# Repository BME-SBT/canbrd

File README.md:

# canbrd
Universal CAN enabled MCU board

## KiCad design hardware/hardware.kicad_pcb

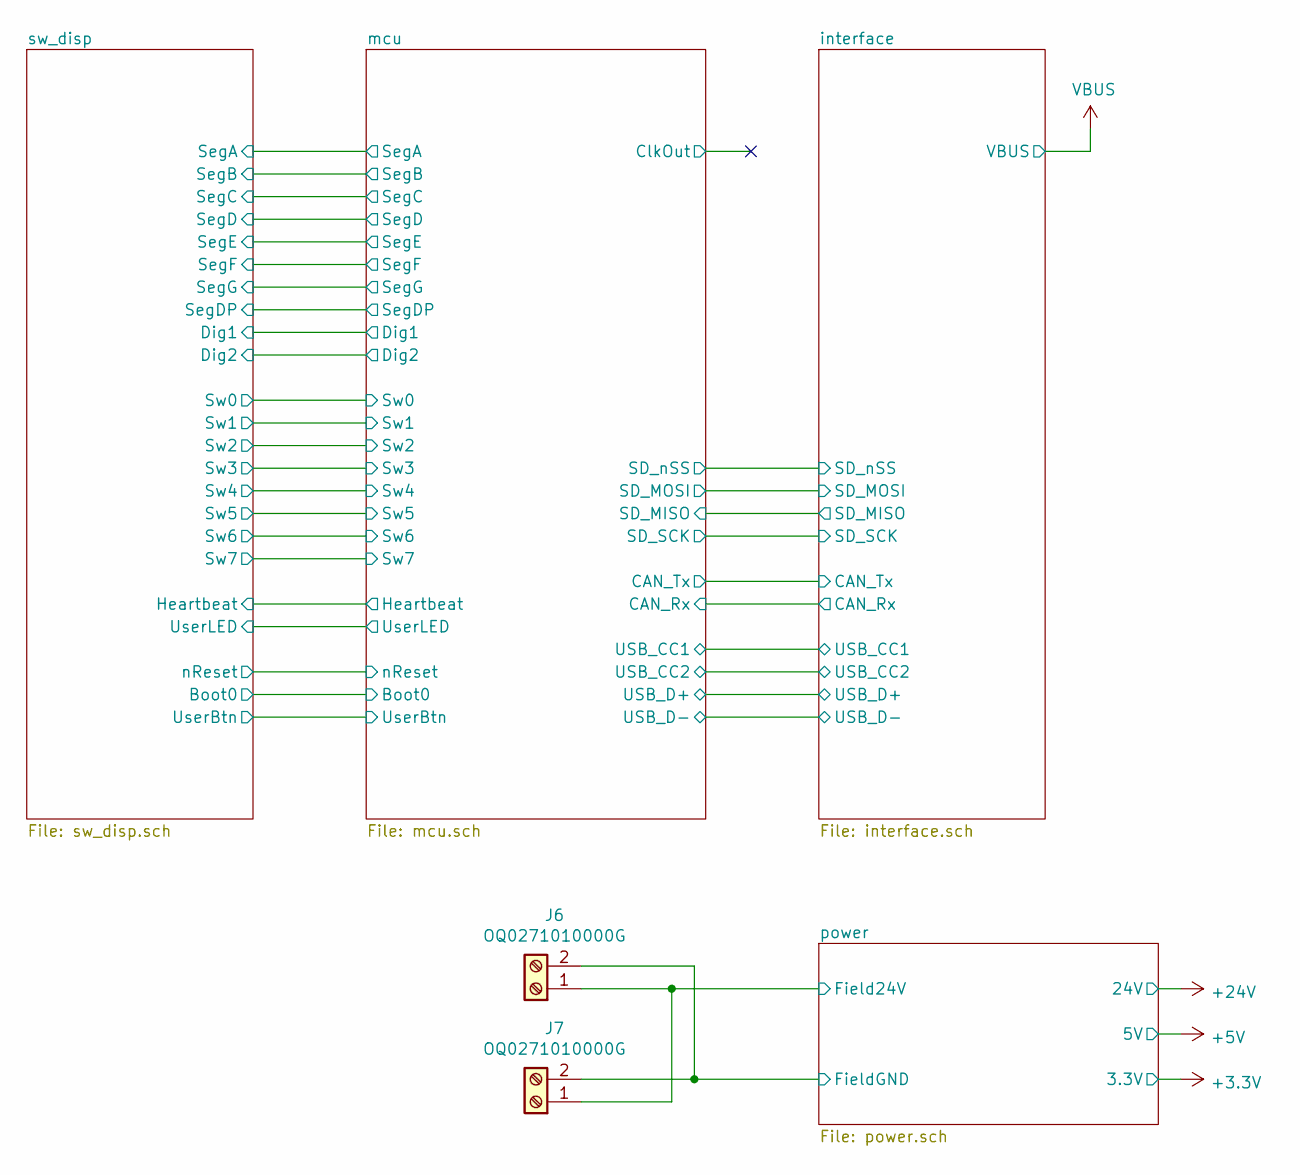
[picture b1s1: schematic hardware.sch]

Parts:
J6, J7: OQ0271010000G; AMPHENOL_OQ0271510000G

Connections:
/power/Field24V: J6.1, J7.1; also elsewhere on the board
/power/FieldGND: J6.2, J7.2; also elsewhere on the board

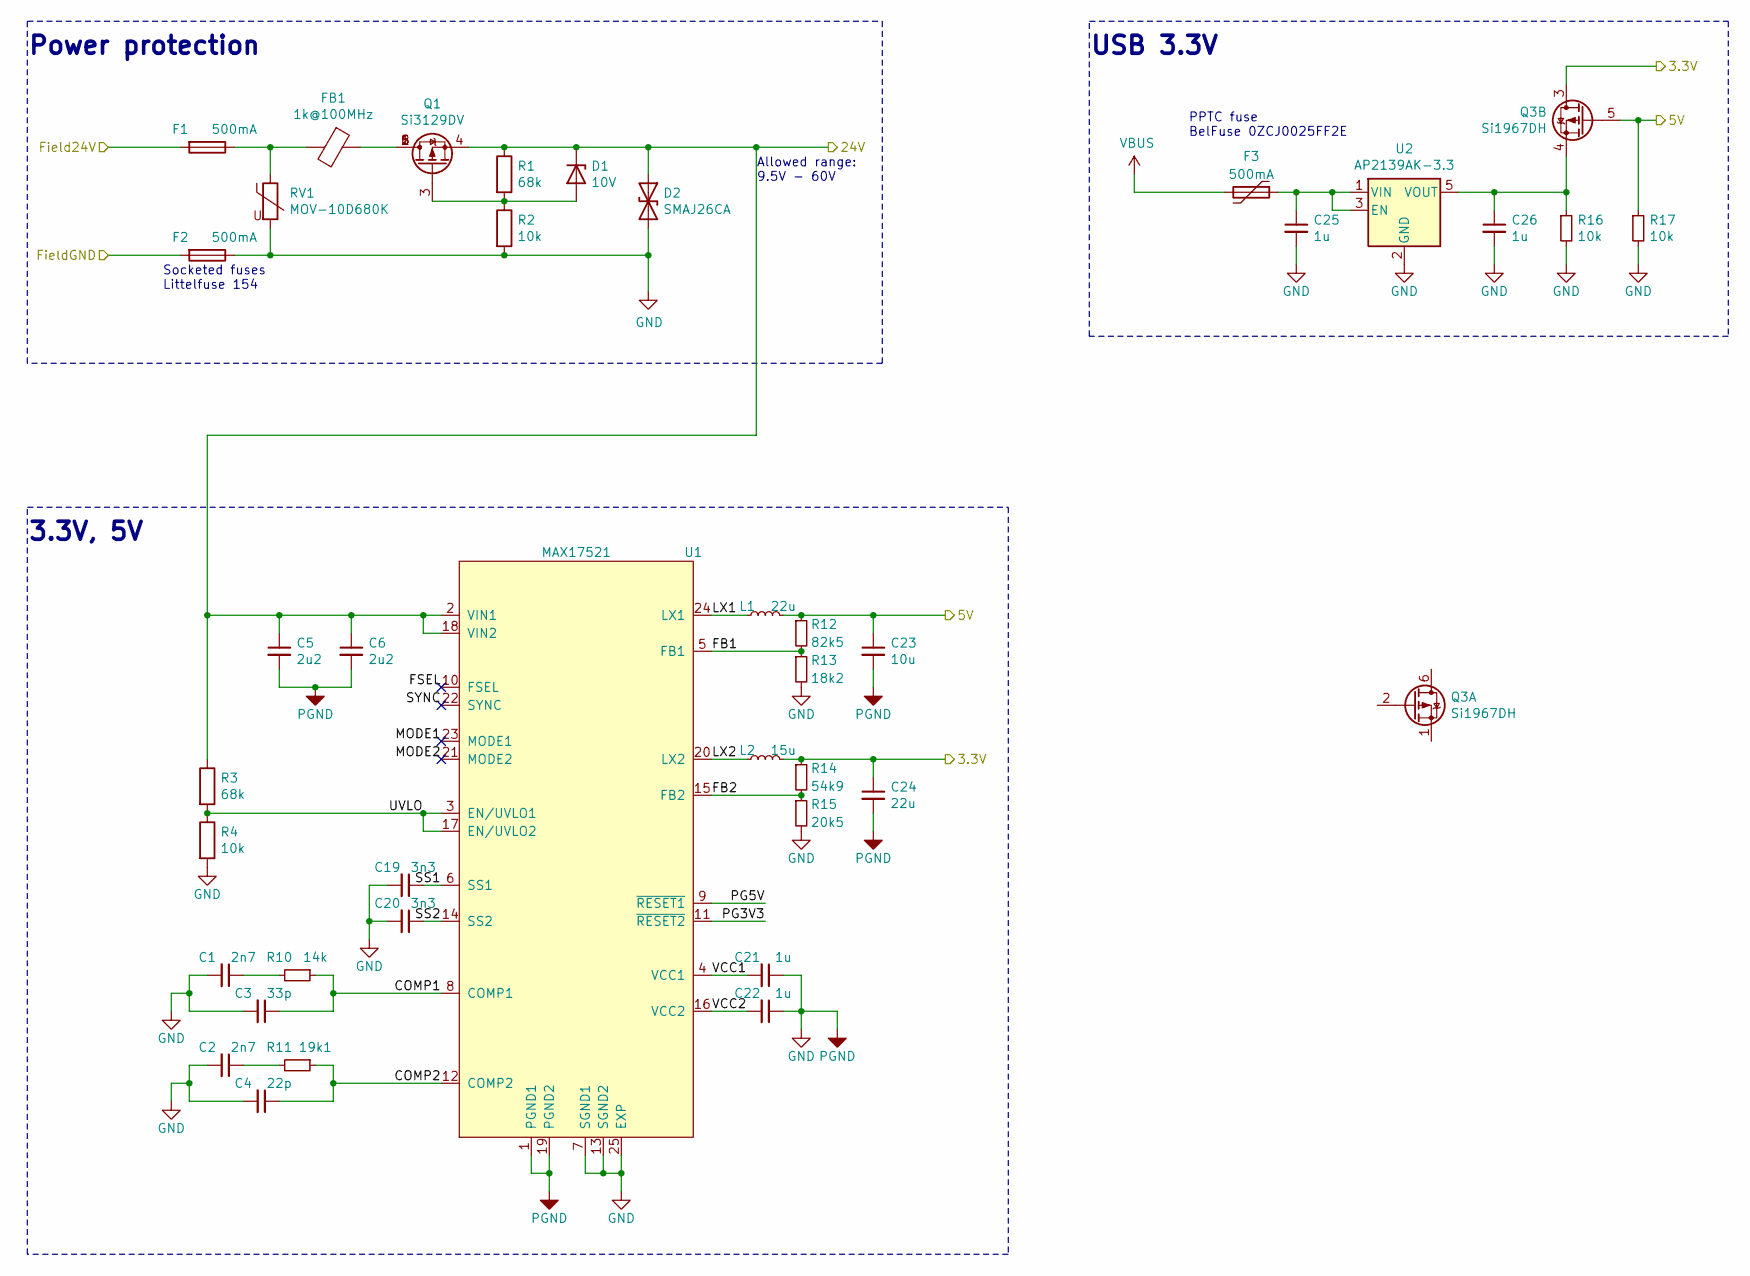
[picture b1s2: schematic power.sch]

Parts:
C1, C2: 2n7; C_0805_2012Metric
C3: 33p; C_0805_2012Metric
C4: 22p; C_0805_2012Metric
C5, C6: 2u2; C_0805_2012Metric
C19, C20: 3n3; C_0805_2012Metric
C21, C22, C25, C26: 1u; C_0805_2012Metric
C23: 10u; C_0805_2012Metric
C24: 22u; C_0805_2012Metric
D1: 10V; D_MiniMELF
D2: SMAJ26CA; D_SMA
F1, F2: 500mA; Littelfuse-154
F3: 500mA; Fuse_1206_3216Metric
FB1: 1k@100MHz; L_0805_2012Metric
L1: 22u; L_Taiyo-Yuden_NR-80xx_HandSoldering; PartNo TaiyoYuden NRS8040T220MJGJ
L2: 15u; L_Taiyo-Yuden_NR-80xx_HandSoldering; PartNo TaiyoYuden NRS8040T150MJGJ
Q1: Si3129DV; TSOP-6_1.65x3.05mm_P0.95mm
Q3: Si1967DH; SOT-363_SC-70-6_Handsoldering
R1, R3: 68k; R_0805_2012Metric
R2, R4, R16, R17: 10k; R_0805_2012Metric
R10: 14k; R_0805_2012Metric
R11: 19k1; R_0805_2012Metric
R12: 82k5; R_0805_2012Metric
R13: 18k2; R_0805_2012Metric
R14: 54k9; R_0805_2012Metric
R15: 20k5; R_0805_2012Metric
RV1: MOV-10D680K; RV_Disc_D12mm_W4.4mm_P7.5mm
U1: MAX17521; QFN50P500X400X80-25N
U2: AP2139AK-3.3; SOT-23-5

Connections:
+3V3: C24.1, L2.2, Q3.3 (D), R14.1; also elsewhere on the board
+5V: C23.1, L1.2, Q3.5 (G), R12.1, R17.1; also elsewhere on the board
/power/COMP1: C3.1, R10.1, U1.8 (COMP1)
/power/COMP2: C4.1, R11.1, U1.12 (COMP2)
/power/FB1: R12.2, R13.1, U1.5 (FB1)
/power/FB2: R14.2, R15.1, U1.15 (FB2)
/power/FSEL: U1.10 (FSEL)
/power/Field24V: F1.2; also elsewhere on the board
/power/FieldGND: F2.2; also elsewhere on the board
/power/LDO_IN: C25.1, F3.1, U2.1 (VIN), U2.3 (EN)
/power/LDO_OUT: C26.1, Q3.4 (S), R16.1, U2.5 (VOUT)
/power/LX1: L1.1, U1.24 (LX1)
/power/LX2: L2.1, U1.20 (LX2)
/power/MODE1: U1.23 (MODE1)
/power/MODE2: U1.21 (MODE2)
/power/PG3V3: U1.11 (~RESET2)
/power/PG5V: U1.9 (~RESET1)
/power/SS1: C19.1, U1.6 (SS1)
/power/SS2: C20.1, U1.14 (SS2)
/power/SYNC: U1.22 (SYNC)
/power/UVLO: R3.2, R4.1, U1.3 (EN/UVLO1), U1.17 (EN/UVLO2)
/power/VCC1: C21.2, U1.4 (VCC1)
/power/VCC2: C22.2, U1.16 (VCC2)
GND: C1.2, C2.2, C3.2, C4.2, C5.2, C6.2, C19.2, C20.2, C21.1, C22.1, C23.2, C24.2, C25.2, C26.2, D2.2 (A2), F2.1, R2.2, R4.2, R13.2, R15.2, R16.2, R17.2, RV1.2, U1.1 (PGND1), U1.7 (SGND1), U1.13 (SGND2), U1.19 (PGND2), U1.25 (EXP), U2.2 (GND); also elsewhere on the board
unnamed: C1.1, R10.2
unnamed: C2.1, R11.2
unnamed: D1.2 (A), Q1.3 (G), R1.2, R2.1
unnamed: FB1.1, Q1.1 (D), Q1.2 (D), Q1.5 (D), Q1.6 (D)
VBUS: F3.2; also elsewhere on the board

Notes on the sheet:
Power protection
Socketed fuses Littelfuse 154
3.3V, 5V
PPTC fuse BelFuse 0ZCJ0025FF2E
Allowed range: 9.5V - 60V
USB 3.3V

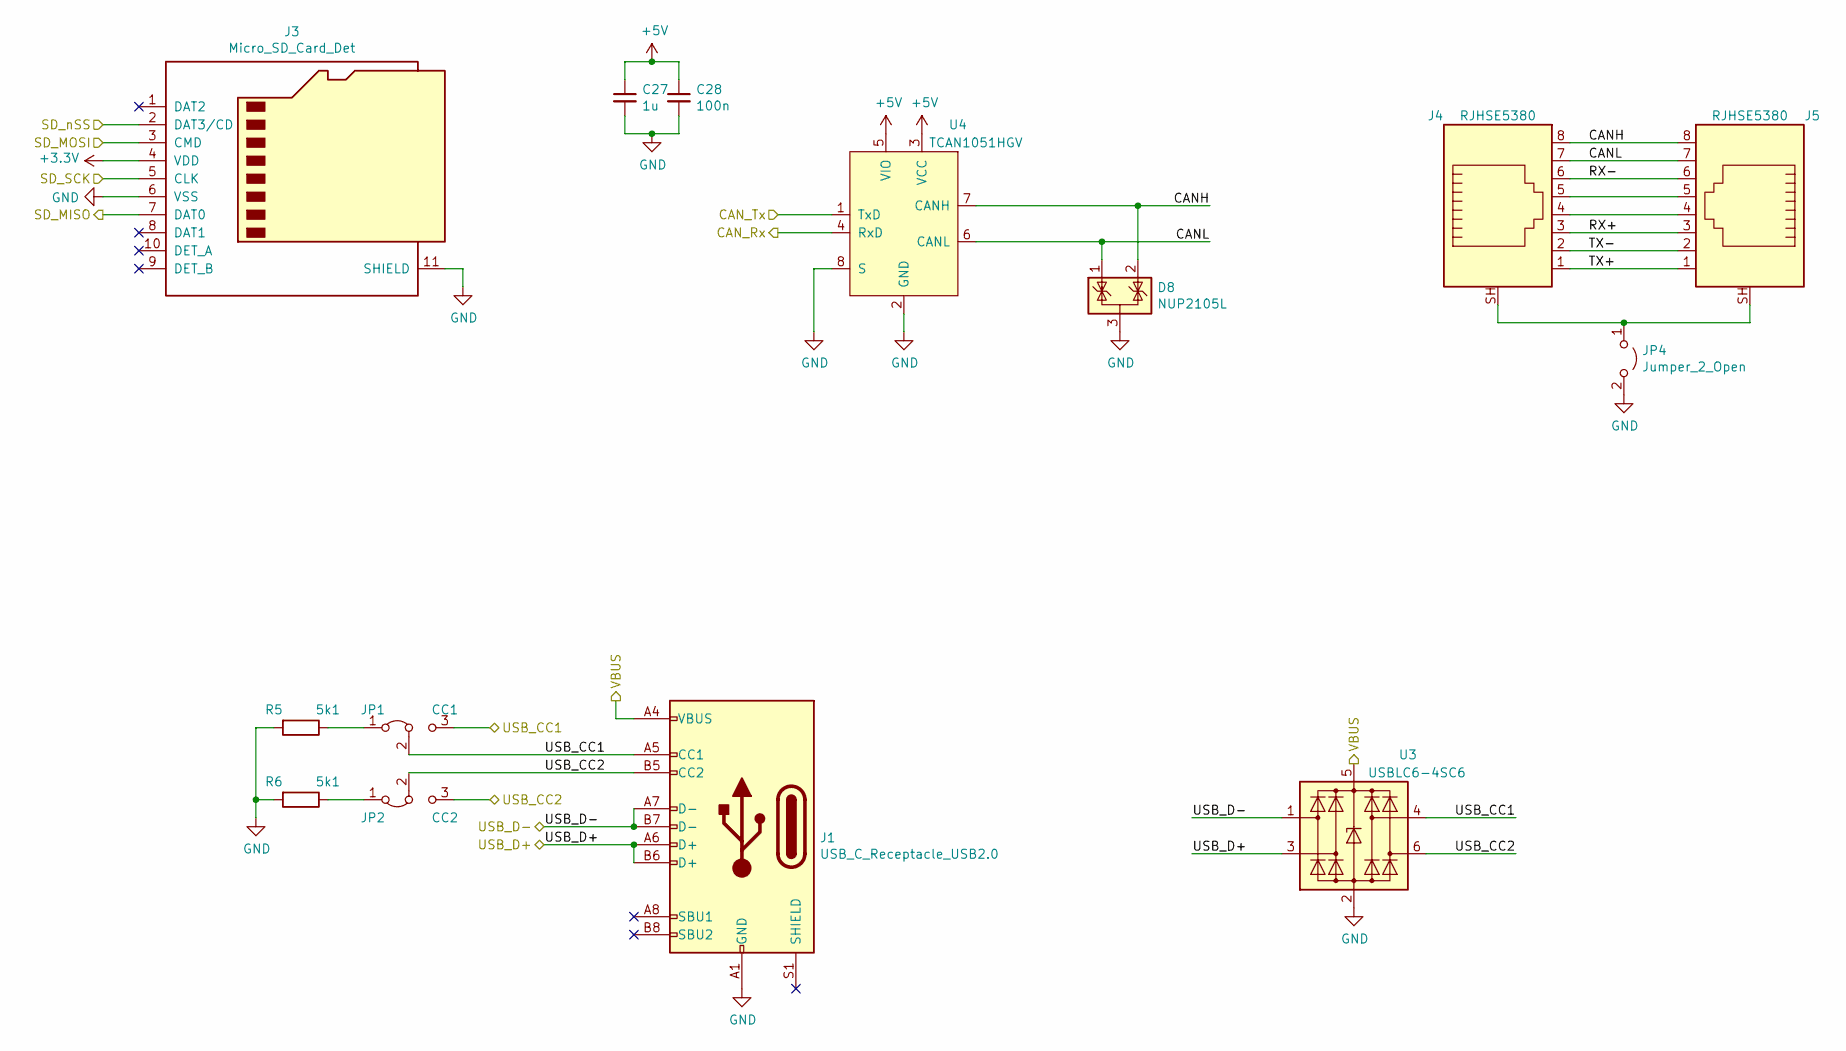
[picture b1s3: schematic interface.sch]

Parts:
C27: 1u; C_0805_2012Metric
C28: 100n; C_0805_2012Metric
D8: NUP2105L; SOT-23
J1: USB_C_Receptacle_USB2.0; USB_C_Receptacle_GCT_USB4085
J3: Micro_SD_Card_Det; microSD_HC_Molex_104031-0811
J4, J5: RJHSE5380; RJ45_Amphenol_RJHSE5380
JP1: CC1; SolderJumper-3_P1.3mm_Bridged12_RoundedPad1.0x1.5mm
JP2: CC2; SolderJumper-3_P1.3mm_Bridged12_RoundedPad1.0x1.5mm
JP4: Jumper_2_Open; SolderJumper-2_P1.3mm_Open_RoundedPad1.0x1.5mm
R5, R6: 5k1; R_0805_2012Metric
U3: USBLC6-4SC6; SOT-23-6
U4: TCAN1051HGV; SOIC-8_3.9x4.9mm_P1.27mm

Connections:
+3V3: J3.4 (VDD); also elsewhere on the board
+5V: C27.1, C28.1, U4.3 (VCC), U4.5 (VIO); also elsewhere on the board
/interface/CANH: D8.2 (K), J4.8, J5.8, U4.7 (CANH)
/interface/CANL: D8.1 (K), J4.7, J5.7, U4.6 (CANL)
/interface/CAN_Rx: U4.4 (RxD); also elsewhere on the board
/interface/CAN_Tx: U4.1 (TxD); also elsewhere on the board
/interface/RX+: J4.3, J5.3
/interface/RX-: J4.6, J5.6
/interface/SD_MISO: J3.7 (DAT0); also elsewhere on the board
/interface/SD_MOSI: J3.3 (CMD); also elsewhere on the board
/interface/SD_SCK: J3.5 (CLK); also elsewhere on the board
/interface/SD_nSS: J3.2 (DAT3/CD); also elsewhere on the board
/interface/TX+: J4.1, J5.1
/interface/TX-: J4.2, J5.2
/interface/USB_CC1: J1.A5 (CC1), JP1.2 (C), JP1.3 (B), U3.4 (I/O3); also elsewhere on the board
/interface/USB_CC2: J1.B5 (CC2), JP2.2 (C), JP2.3 (B), U3.6 (I/O4); also elsewhere on the board
/interface/USB_D+: J1.A6 (D+), J1.B6 (D+), U3.3 (I/O2); also elsewhere on the board
/interface/USB_D-: J1.A7 (D-), J1.B7 (D-), U3.1 (I/O1); also elsewhere on the board
GND: C27.2, C28.2, D8.3 (A), J1.A1 (GND), J1.A12 (GND), J1.B1 (GND), J1.B12 (GND), J3.6 (VSS), J3.11 (SHIELD), JP4.2 (B), R5.2, R6.2, U3.2 (GND), U4.2 (GND), U4.8 (S); also elsewhere on the board
unnamed: J4.4, J5.4
unnamed: J4.5, J5.5
unnamed: J4.SH, J5.SH, JP4.1 (A)
unnamed: JP1.1 (A), R5.1
unnamed: JP2.1 (A), R6.1
VBUS: J1.A4 (VBUS), J1.A9 (VBUS), J1.B4 (VBUS), J1.B9 (VBUS), U3.5 (VBUS); also elsewhere on the board

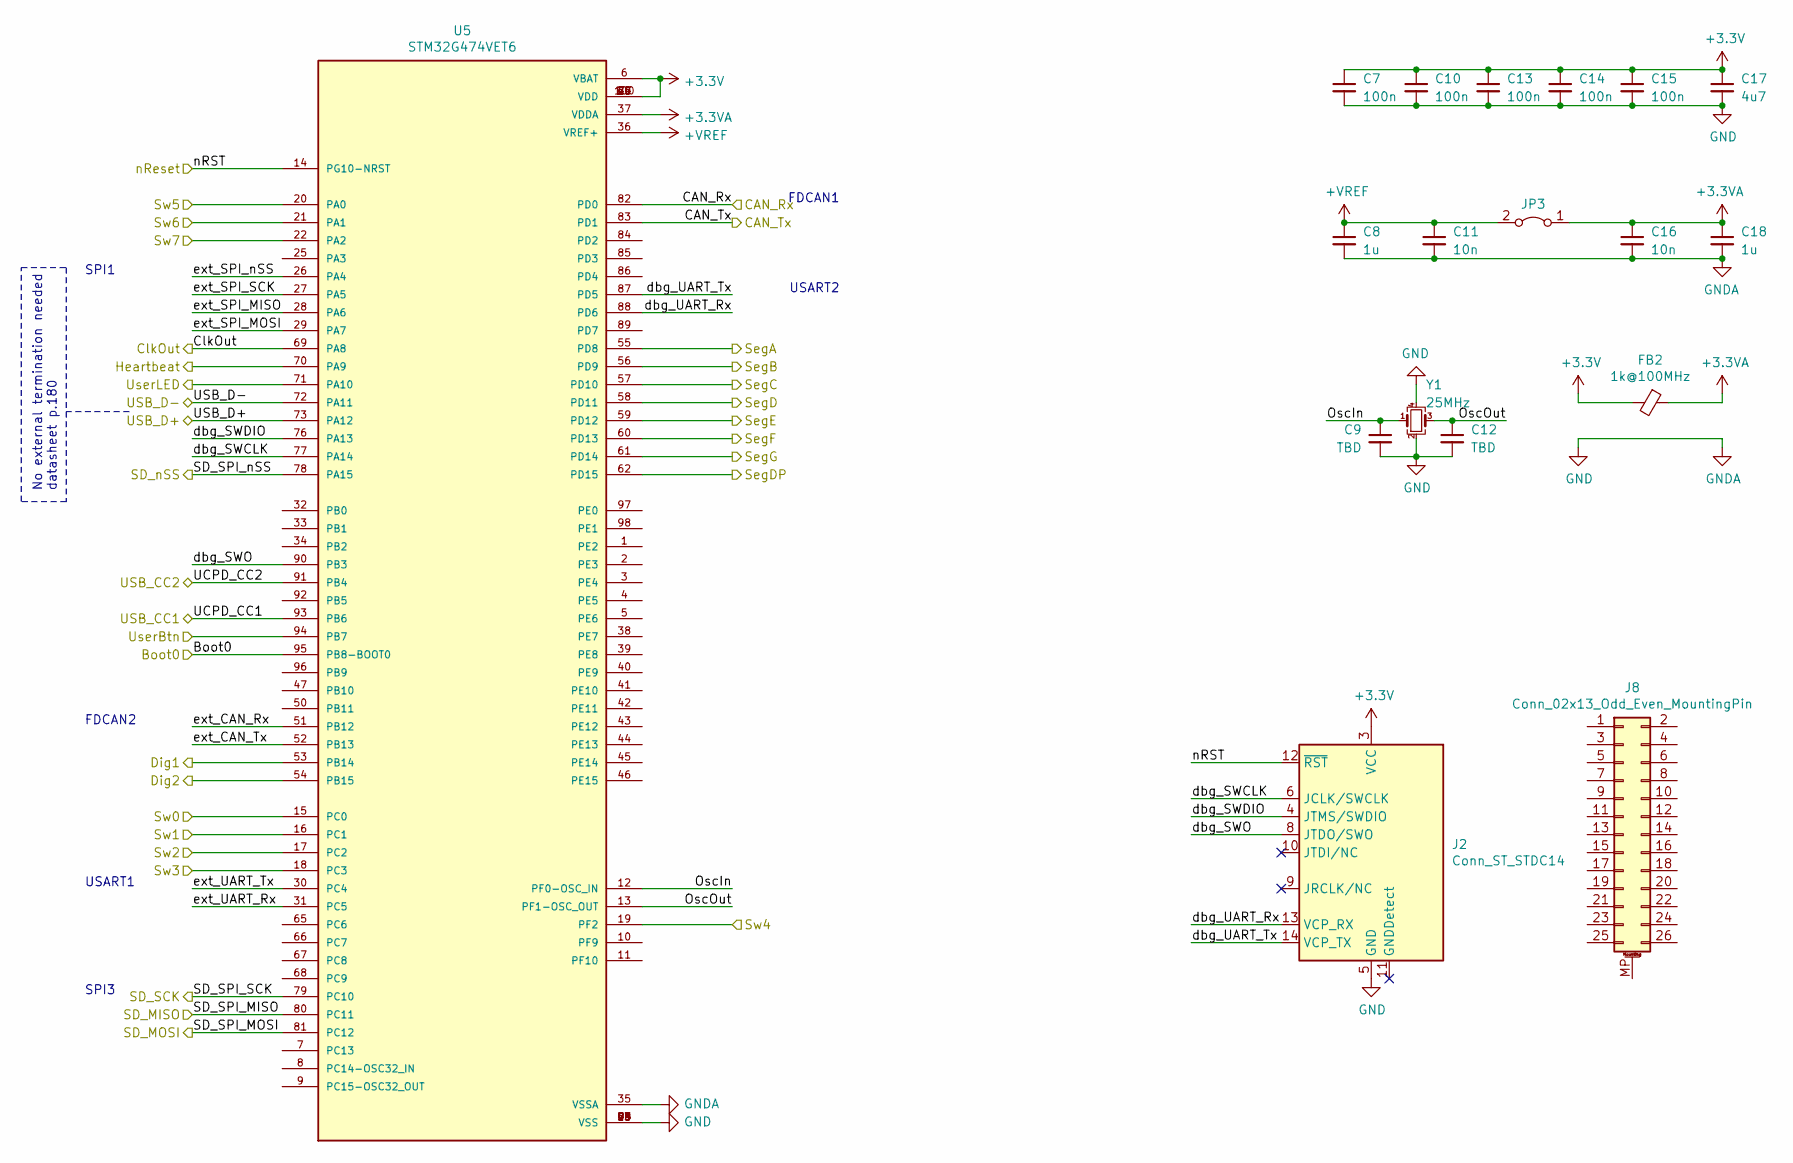
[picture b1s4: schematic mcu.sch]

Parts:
C7, C10, C13, C14, C15: 100n; C_0805_2012Metric
C8, C18: 1u; C_0805_2012Metric
C9, C12: TBD; C_0805_2012Metric
C11, C16: 10n; C_0805_2012Metric
C17: 4u7; C_0805_2012Metric
FB2: 1k@100MHz; L_0805_2012Metric
J2: Conn_ST_STDC14; PinHeader_2x07_P1.27mm_Vertical_SMD
J8: Conn_02x13_Odd_Even_MountingPin; IDC-Header_2x13-1MP_P2.54mm_Latch_Horizontal
JP3: Jumper_2_Bridged; SolderJumper-2_P1.3mm_Bridged_RoundedPad1.0x1.5mm
U5: STM32G474VET6; TQFP-100_14x14mm_P0.5mm; PARTREV 2
Y1: 25MHz; Crystal_SMD_3225-4Pin_3.2x2.5mm_HandSoldering

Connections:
+3.3VA: C16.1, C18.1, FB2.1, JP3.1 (A), U5.37 (VDDA)
+3V3: C7.1, C10.1, C13.1, C14.1, C15.1, C17.1, FB2.2, J2.3 (VCC), U5.6 (VBAT), U5.24 (VDD), U5.49 (VDD), U5.64 (VDD), U5.75 (VDD), U5.100 (VDD); also elsewhere on the board
/interface/CAN_Rx: U5.82 (PD0); also elsewhere on the board
/interface/CAN_Tx: U5.83 (PD1); also elsewhere on the board
/interface/SD_MISO: U5.80 (PC11); also elsewhere on the board
/interface/SD_MOSI: U5.81 (PC12); also elsewhere on the board
/interface/SD_SCK: U5.79 (PC10); also elsewhere on the board
/interface/SD_nSS: U5.78 (PA15); also elsewhere on the board
/interface/USB_CC1: U5.93 (PB6); also elsewhere on the board
/interface/USB_CC2: U5.91 (PB4); also elsewhere on the board
/interface/USB_D+: U5.73 (PA12); also elsewhere on the board
/interface/USB_D-: U5.72 (PA11); also elsewhere on the board
/mcu/Boot0: U5.95 (PB8-BOOT0); also elsewhere on the board
/mcu/ClkOut: U5.69 (PA8)
/mcu/Dig1: U5.53 (PB14); also elsewhere on the board
/mcu/Dig2: U5.54 (PB15); also elsewhere on the board
/mcu/Heartbeat: U5.70 (PA9); also elsewhere on the board
/mcu/OscIn: C9.1, U5.12 (PF0-OSC_IN), Y1.1
/mcu/OscOut: C12.1, U5.13 (PF1-OSC_OUT), Y1.3
/mcu/SegA: U5.55 (PD8); also elsewhere on the board
/mcu/SegB: U5.56 (PD9); also elsewhere on the board
/mcu/SegC: U5.57 (PD10); also elsewhere on the board
/mcu/SegD: U5.58 (PD11); also elsewhere on the board
/mcu/SegDP: U5.62 (PD15); also elsewhere on the board
/mcu/SegE: U5.59 (PD12); also elsewhere on the board
/mcu/SegF: U5.60 (PD13); also elsewhere on the board
/mcu/SegG: U5.61 (PD14); also elsewhere on the board
/mcu/Sw0: U5.15 (PC0); also elsewhere on the board
/mcu/Sw1: U5.16 (PC1); also elsewhere on the board
/mcu/Sw2: U5.17 (PC2); also elsewhere on the board
/mcu/Sw3: U5.18 (PC3); also elsewhere on the board
/mcu/Sw4: U5.19 (PF2); also elsewhere on the board
/mcu/Sw5: U5.20 (PA0); also elsewhere on the board
/mcu/Sw6: U5.21 (PA1); also elsewhere on the board
/mcu/Sw7: U5.22 (PA2); also elsewhere on the board
/mcu/UserBtn: U5.94 (PB7); also elsewhere on the board
/mcu/UserLED: U5.71 (PA10); also elsewhere on the board
/mcu/dbg_SWCLK: J2.6 (JCLK/SWCLK), U5.77 (PA14)
/mcu/dbg_SWDIO: J2.4 (JTMS/SWDIO), U5.76 (PA13)
/mcu/dbg_SWO: J2.8 (JTDO/SWO), U5.90 (PB3)
/mcu/dbg_UART_Rx: J2.13 (VCP_RX), U5.88 (PD6)
/mcu/dbg_UART_Tx: J2.14 (VCP_TX), U5.87 (PD5)
/mcu/ext_CAN_Rx: U5.51 (PB12)
/mcu/ext_CAN_Tx: U5.52 (PB13)
/mcu/ext_SPI_MISO: U5.28 (PA6)
/mcu/ext_SPI_MOSI: U5.29 (PA7)
/mcu/ext_SPI_SCK: U5.27 (PA5)
/mcu/ext_SPI_nSS: U5.26 (PA4)
/mcu/ext_UART_Rx: U5.31 (PC5)
/mcu/ext_UART_Tx: U5.30 (PC4)
/mcu/nReset: J2.12 (~RST), U5.14 (PG10-NRST); also elsewhere on the board
GND: C7.2, C8.2, C9.2, C10.2, C11.2, C12.2, C13.2, C14.2, C15.2, C16.2, C17.2, C18.2, J2.5 (GND), J2.7 (GND), U5.23 (VSS), U5.35 (VSSA), U5.48 (VSS), U5.63 (VSS), U5.74 (VSS), U5.99 (VSS), Y1.2, Y1.4; also elsewhere on the board

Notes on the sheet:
SPI1
FDCAN2
USART1
USART2
SPI3
FDCAN1
No external termination needed datasheet p.180

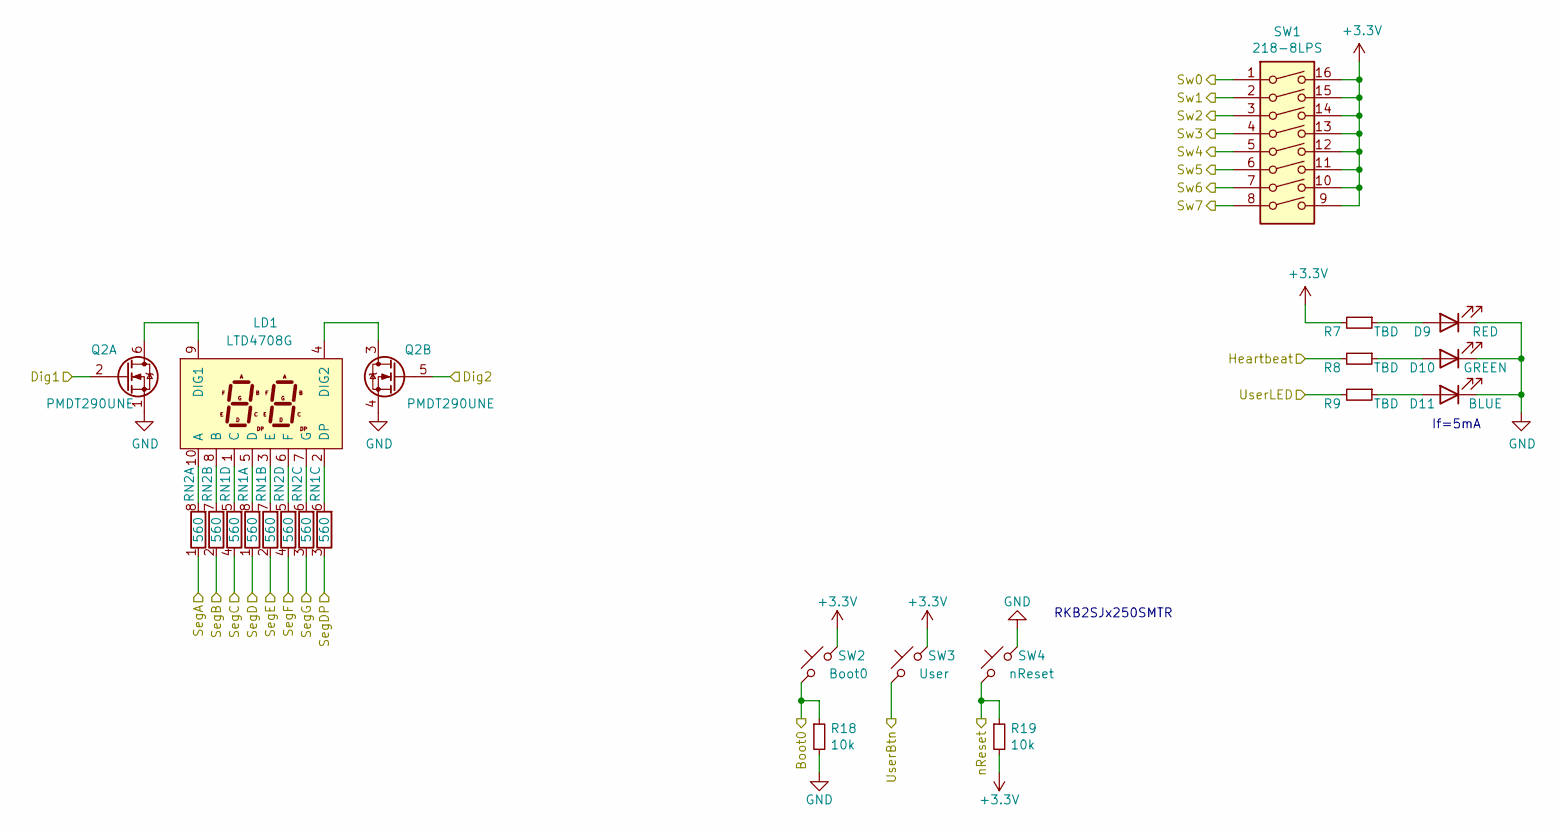
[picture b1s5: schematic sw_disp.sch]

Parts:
D9: RED; LED_0805_2012Metric
D10: GREEN; LED_0805_2012Metric
D11: BLUE; LED_0805_2012Metric
LD1: LTD4708G; LED_LTD-4708G
Q2: PMDT290UNE; SOT-666
R7, R8, R9: TBD; R_0805_2012Metric
R18, R19: 10k; R_0805_2012Metric
RN1, RN2: 560; R_Array_Concave_4x0603
SW1: 218-8LPS; SW_DIP_SPSTx08_Slide_KingTek_DSHP08TS_W7.62mm_P1.27mm
SW2: Boot0; RKB2SJ
SW3: User; RKB2SJ
SW4: nReset; RKB2SJ

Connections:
+3V3: R7.2, R19.2, SW1.9, SW1.10, SW1.11, SW1.12, SW1.13, SW1.14, SW1.15, SW1.16, SW2.2, SW3.2; also elsewhere on the board
/mcu/Boot0: R18.1, SW2.1; also elsewhere on the board
/mcu/Dig1: Q2.2 (G); also elsewhere on the board
/mcu/Dig2: Q2.5 (G); also elsewhere on the board
/mcu/Heartbeat: R8.2; also elsewhere on the board
/mcu/SegA: RN2.1 (R1.1); also elsewhere on the board
/mcu/SegB: RN2.2 (R2.1); also elsewhere on the board
/mcu/SegC: RN1.4 (R4.1); also elsewhere on the board
/mcu/SegD: RN1.1 (R1.1); also elsewhere on the board
/mcu/SegDP: RN1.3 (R3.1); also elsewhere on the board
/mcu/SegE: RN1.2 (R2.1); also elsewhere on the board
/mcu/SegF: RN2.4 (R4.1); also elsewhere on the board
/mcu/SegG: RN2.3 (R3.1); also elsewhere on the board
/mcu/Sw0: SW1.1; also elsewhere on the board
/mcu/Sw1: SW1.2; also elsewhere on the board
/mcu/Sw2: SW1.3; also elsewhere on the board
/mcu/Sw3: SW1.4; also elsewhere on the board
/mcu/Sw4: SW1.5; also elsewhere on the board
/mcu/Sw5: SW1.6; also elsewhere on the board
/mcu/Sw6: SW1.7; also elsewhere on the board
/mcu/Sw7: SW1.8; also elsewhere on the board
/mcu/UserBtn: SW3.1; also elsewhere on the board
/mcu/UserLED: R9.2; also elsewhere on the board
/mcu/nReset: R19.1, SW4.1; also elsewhere on the board
GND: D9.1 (K), D10.1 (K), D11.1 (K), Q2.1 (S), Q2.4 (S), R18.2, SW4.2; also elsewhere on the board
unnamed: D9.2 (A), R7.1
unnamed: D10.2 (A), R8.1
unnamed: D11.2 (A), R9.1
unnamed: LD1.1 (C), RN1.5 (R4.2)
unnamed: LD1.2 (DP), RN1.6 (R3.2)
unnamed: LD1.3 (E), RN1.7 (R2.2)
unnamed: LD1.4 (DIG2), Q2.3 (D)
unnamed: LD1.5 (D), RN1.8 (R1.2)
unnamed: LD1.6 (F), RN2.5 (R4.2)
unnamed: LD1.7 (G), RN2.6 (R3.2)
unnamed: LD1.8 (B), RN2.7 (R2.2)
unnamed: LD1.9 (DIG1), Q2.6 (D)
unnamed: LD1.10 (A), RN2.8 (R1.2)

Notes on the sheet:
If=5mA
RKB2SJx250SMTR

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
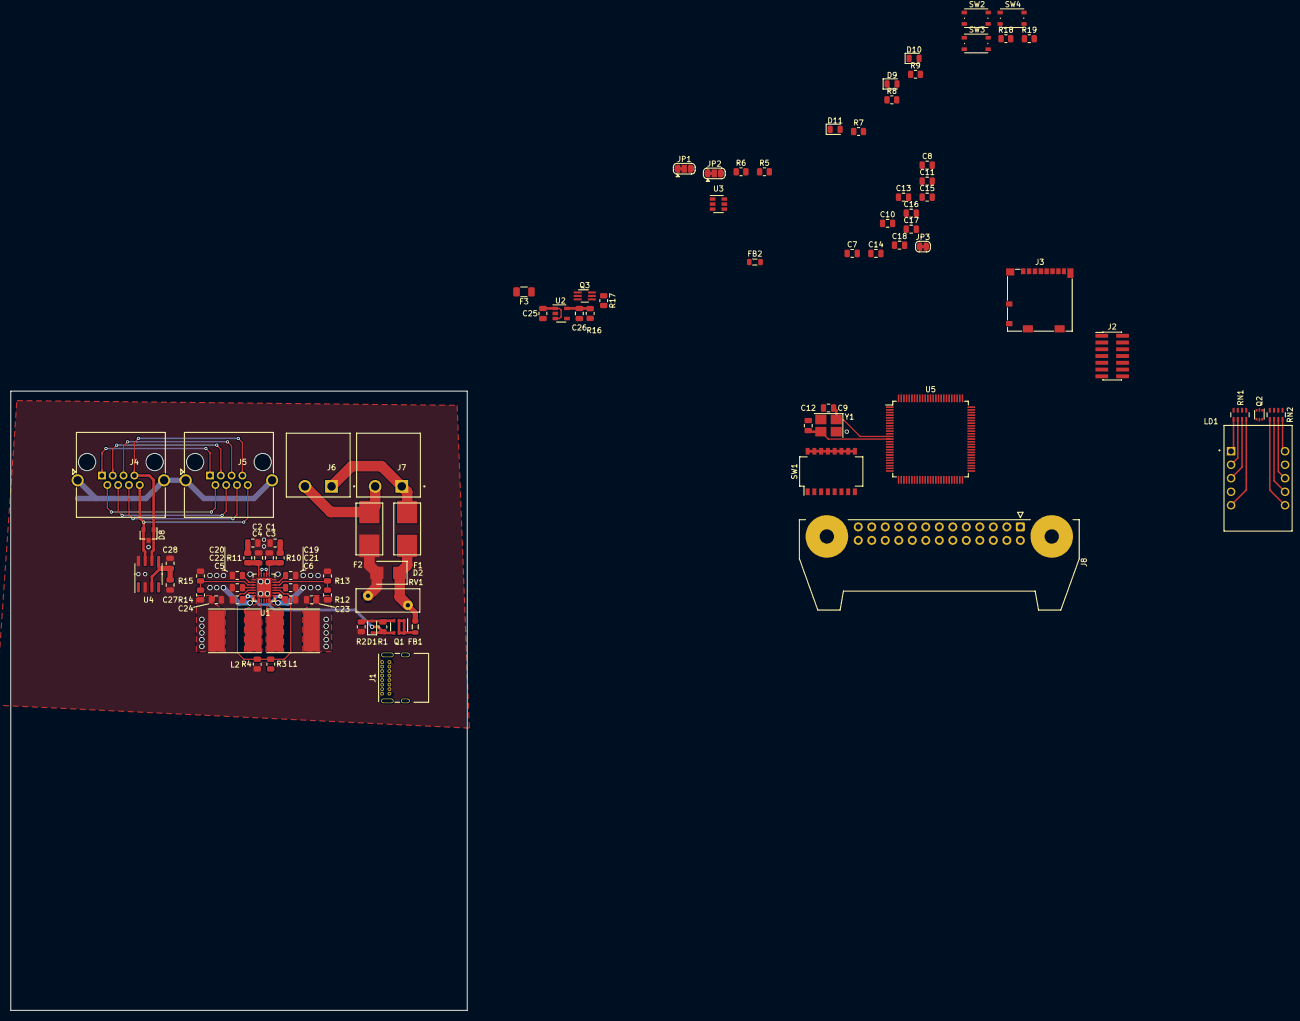
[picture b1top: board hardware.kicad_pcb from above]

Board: 2 copper layers, 85.9 x 116.5 mm, 89 parts (1 on the bottom side), 91 nets.

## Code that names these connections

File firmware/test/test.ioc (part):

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Mcu.Name=STM32G474V(B-C-E)Tx
Mcu.Package=LQFP100
Mcu.UserName=STM32G474VETx
PA0.GPIOParameters=GPIO_PuPd,GPIO_Label,GPIO_Mode
PA0.GPIO_Label=Sw5
PA0.GPIO_Mode=GPIO_MODE_INPUT
PA0.GPIO_PuPd=GPIO_PULLDOWN
PA0.Signal=GPIO_Input
PA1.GPIOParameters=GPIO_PuPd,GPIO_Label,GPIO_Mode
PA1.GPIO_Label=Sw6
PA1.GPIO_Mode=GPIO_MODE_INPUT
PA1.GPIO_PuPd=GPIO_PULLDOWN
PA1.Signal=GPIO_Input
PA10.GPIOParameters=GPIO_Speed,PinState,GPIO_PuPd,GPIO_Label,GPIO_ModeDefaultOutputPP
PA10.GPIO_Label=UserLED
PA10.GPIO_ModeDefaultOutputPP=GPIO_MODE_OUTPUT_PP
PA10.GPIO_PuPd=GPIO_NOPULL
PA10.GPIO_Speed=GPIO_SPEED_FREQ_MEDIUM
PA10.PinState=GPIO_PIN_RESET
PA10.Signal=GPIO_Output
PA11.Mode=Device
PA11.Signal=USB_DM
PA12.Mode=Device
PA12.Signal=USB_DP
PA13.Mode=Serial_Wire
PA13.Signal=SYS_JTMS-SWDIO
PA14.Mode=Serial_Wire
PA14.Signal=SYS_JTCK-SWCLK
PA15.Mode=NSS_Signal_Hard_Output
PA15.Signal=SPI3_NSS
PA2.GPIOParameters=GPIO_PuPd,GPIO_Label,GPIO_Mode
PA2.GPIO_Label=Sw7
PA2.GPIO_Mode=GPIO_MODE_INPUT
PA2.GPIO_PuPd=GPIO_PULLDOWN
PA2.Signal=GPIO_Input
PA4.GPIOParameters=GPIO_Label
PA4.GPIO_Label=ext_SPI_nSS
PA4.Mode=NSS_Signal_Hard_Output
PA4.Signal=SPI1_NSS
PA5.GPIOParameters=GPIO_Label
PA5.GPIO_Label=ext_SPI_SCK
PA5.Mode=Full_Duplex_Master
PA5.Signal=SPI1_SCK
PA6.GPIOParameters=GPIO_Label
PA6.GPIO_Label=ext_SPI_MISO
PA6.Mode=Full_Duplex_Master
PA6.Signal=SPI1_MISO
PA7.GPIOParameters=GPIO_Label
PA7.GPIO_Label=ext_SPI_MOSI
PA7.Mode=Full_Duplex_Master
PA7.Signal=SPI1_MOSI
PA8.Mode=Clock-out
PA8.Signal=RCC_MCO
PA9.GPIOParameters=GPIO_Speed,PinState,GPIO_PuPd,GPIO_Label,GPIO_ModeDefaultOutputPP
PA9.GPIO_Label=Heartbeat
PA9.GPIO_ModeDefaultOutputPP=GPIO_MODE_OUTPUT_PP
PA9.GPIO_PuPd=GPIO_NOPULL
PA9.GPIO_Speed=GPIO_SPEED_FREQ_LOW
PA9.PinState=GPIO_PIN_RESET
PA9.Signal=GPIO_Output
PB12.GPIOParameters=GPIO_Label
PB12.GPIO_Label=ext_CAN_Rx
PB12.Mode=FDCAN_Activate
PB12.Signal=FDCAN2_RX
PB13.GPIOParameters=GPIO_Label
PB13.GPIO_Label=ext_CAN_Tx
PB13.Mode=FDCAN_Activate
PB13.Signal=FDCAN2_TX
PB14.GPIOParameters=GPIO_Label
PB14.GPIO_Label=Dig1
PB14.Signal=GPIO_Output
PB15.GPIOParameters=GPIO_Label
PB15.GPIO_Label=Dig2
PB15.Signal=GPIO_Output
PB3.Signal=SYS_JTDO-SWO
PB4.Signal=UCPD1_CC2
PB6.Signal=UCPD1_CC1
PB7.GPIOParameters=GPIO_Label
PB7.GPIO_Label=UserBtn
PB7.Signal=GPIO_Input
PC0.GPIOParameters=GPIO_PuPd,GPIO_Label,GPIO_Mode
PC0.GPIO_Label=Sw0
PC0.GPIO_Mode=GPIO_MODE_INPUT
PC0.GPIO_PuPd=GPIO_PULLDOWN
PC0.Signal=GPIO_Input
PC1.GPIOParameters=GPIO_PuPd,GPIO_Label,GPIO_Mode
PC1.GPIO_Label=Sw1
PC1.GPIO_Mode=GPIO_MODE_INPUT
PC1.GPIO_PuPd=GPIO_PULLDOWN
PC1.Signal=GPIO_Input
PC10.Mode=Full_Duplex_Master
PC10.Signal=SPI3_SCK
PC11.Mode=Full_Duplex_Master
PC11.Signal=SPI3_MISO
PC12.Mode=Full_Duplex_Master
PC12.Signal=SPI3_MOSI
PC2.GPIOParameters=GPIO_PuPd,GPIO_Label,GPIO_Mode
PC2.GPIO_Label=Sw2
PC2.GPIO_Mode=GPIO_MODE_INPUT
PC2.GPIO_PuPd=GPIO_PULLDOWN
PC2.Signal=GPIO_Input
PC3.GPIOParameters=GPIO_PuPd,GPIO_Label,GPIO_Mode
PC3.GPIO_Label=Sw3
PC3.GPIO_Mode=GPIO_MODE_INPUT
PC3.GPIO_PuPd=GPIO_PULLDOWN
PC3.Signal=GPIO_Input
PC4.GPIOParameters=GPIO_Label
PC4.GPIO_Label=ext_UART_Tx
PC4.Mode=Asynchronous
PC4.Signal=USART1_TX
PC5.GPIOParameters=GPIO_Label
PC5.GPIO_Label=ext_UART_Rx
PC5.Mode=Asynchronous
PC5.Signal=USART1_RX
PC6.GPIOParameters=GPIO_Label
PC6.GPIO_Label=ext_I2C_SCL
PC6.Mode=I2C
PC6.Signal=I2C4_SCL
PC7.GPIOParameters=GPIO_Label
PC7.GPIO_Label=ext_I2C_SDA
PC7.Mode=I2C
PC7.Signal=I2C4_SDA
PD0.Mode=FDCAN_Activate
PD0.Signal=FDCAN1_RX
PD1.Mode=FDCAN_Activate
PD1.Signal=FDCAN1_TX
PD10.GPIOParameters=GPIO_Label
PD10.GPIO_Label=SegC
PD10.Signal=GPIO_Output
PD11.GPIOParameters=GPIO_Label
PD11.GPIO_Label=SegD
PD11.Signal=GPIO_Output
PD12.GPIOParameters=GPIO_Label
PD12.GPIO_Label=SegE
PD12.Signal=GPIO_Output
PD13.GPIOParameters=GPIO_Label
PD13.GPIO_Label=SegF
PD13.Signal=GPIO_Output
PD14.GPIOParameters=GPIO_Label
PD14.GPIO_Label=SegG
PD14.Signal=GPIO_Output
PD15.GPIOParameters=GPIO_Label
PD15.GPIO_Label=SegDP
PD15.Signal=GPIO_Output
PD5.Mode=Asynchronous
PD5.Signal=USART2_TX
PD6.Mode=Asynchronous
PD6.Signal=USART2_RX
PD8.GPIOParameters=GPIO_Label
PD8.GPIO_Label=SegA
PD8.Signal=GPIO_Output
PD9.GPIOParameters=GPIO_Label
PD9.GPIO_Label=SegB
PD9.Signal=GPIO_Output
PE2.Signal=SPI4_SCK
PE3.Signal=SPI4_NSS
PE5.Signal=SPI4_MISO
PE6.Signal=SPI4_MOSI
PF0-OSC_IN.Mode=HSE-External-Oscillator
PF0-OSC_IN.Signal=RCC_OSC_IN
PF1-OSC_OUT.Mode=HSE-External-Oscillator
PF1-OSC_OUT.Signal=RCC_OSC_OUT
PF2.GPIOParameters=GPIO_PuPd,GPIO_Label,GPIO_Mode
PF2.GPIO_Label=Sw4
PF2.GPIO_Mode=GPIO_MODE_INPUT
PF2.GPIO_PuPd=GPIO_PULLDOWN
PF2.Signal=GPIO_Input
RCC.HSE_VALUE=25000000
RCC.SYSCLKFreq_VALUE=170000000
RCC.SYSCLKSource=RCC_SYSCLKSOURCE_PLLCLK
board=custom

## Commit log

2021-08-03 things changed
2021-08-03 stm32f722vetx
2021-08-03 Add gitignore
2021-08-04 stm32f722retx
2021-08-05 stm32g474vetx
2021-08-08 updated to stm32g474vetx
2021-08-16 Start hardware
2021-08-17 WIP: schematic
2021-08-19 Change power protection
2021-08-19 Power looks nice
2021-08-22 Changed power again
2021-08-23 Started routing
2021-08-24 Power routing
